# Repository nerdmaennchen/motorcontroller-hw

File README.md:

A somewhat easy to build two-layer PCB to controll BLDC-motors with.

The board is designed to have:
	- USB connection (every computer has a USB port but there are virtually no boards out there that offer a USB connection (without an FTDI in between))
	- up to 200W (tested) output power (theoretical -- when ignoring trace resistances -- maximum 900W)
	- digital Hall-Encoder interface
	- analog/absolute hall-encoder interface
	- BEMF measurement for hall-less operation
	- serial interface to cascade multiple BLDC-drivers over one USB interface
	- two PWM outputs for RC-servo motors
	- one connector to attach WS2812b LEDs
	- a layout that allows somewhat easy manufacturing by placing most parts on one layer (I've once built 15 pieces in 8h by hand soldering)
	
The board has four power domains:
	- internal 3.3V -- to power the microcontroller
	- USB-5V -- can power the internal 3.3V domain; protected from the external 5V domain with a diode thus protecting the USB-host from voltage spikes on the external 5V-domain
	- external 5V -- can power the internal 3.3V domain; powers the WS2812b LEDs and RC-servo motors

The board utilizes an STM32F401xx processor which is super nice to program, debug and due to its QFN48 footprint super easy to solder by hand -- as long as you have access to a rework station.
Software for the uC can be found here: https://github.com/nerdmaennchen/motorcontroller-uc-sw
Software for the USB-Host here: https://github.com/nerdmaennchen/motorcontroller-sw

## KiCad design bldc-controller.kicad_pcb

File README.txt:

Hey Lutz,

hier Adrian von FRT...wollte nochmal nachfragen wie's aussieht?
Wenn ich den vorletztten Commit richtig verstanden habe, gibt's ja
ne gut funktionierende Variante?

Sry, das ich da sonen bisschen Druck machen muss, aber uns läuft 
lamgsam die Zeit davon...

LG Adrian

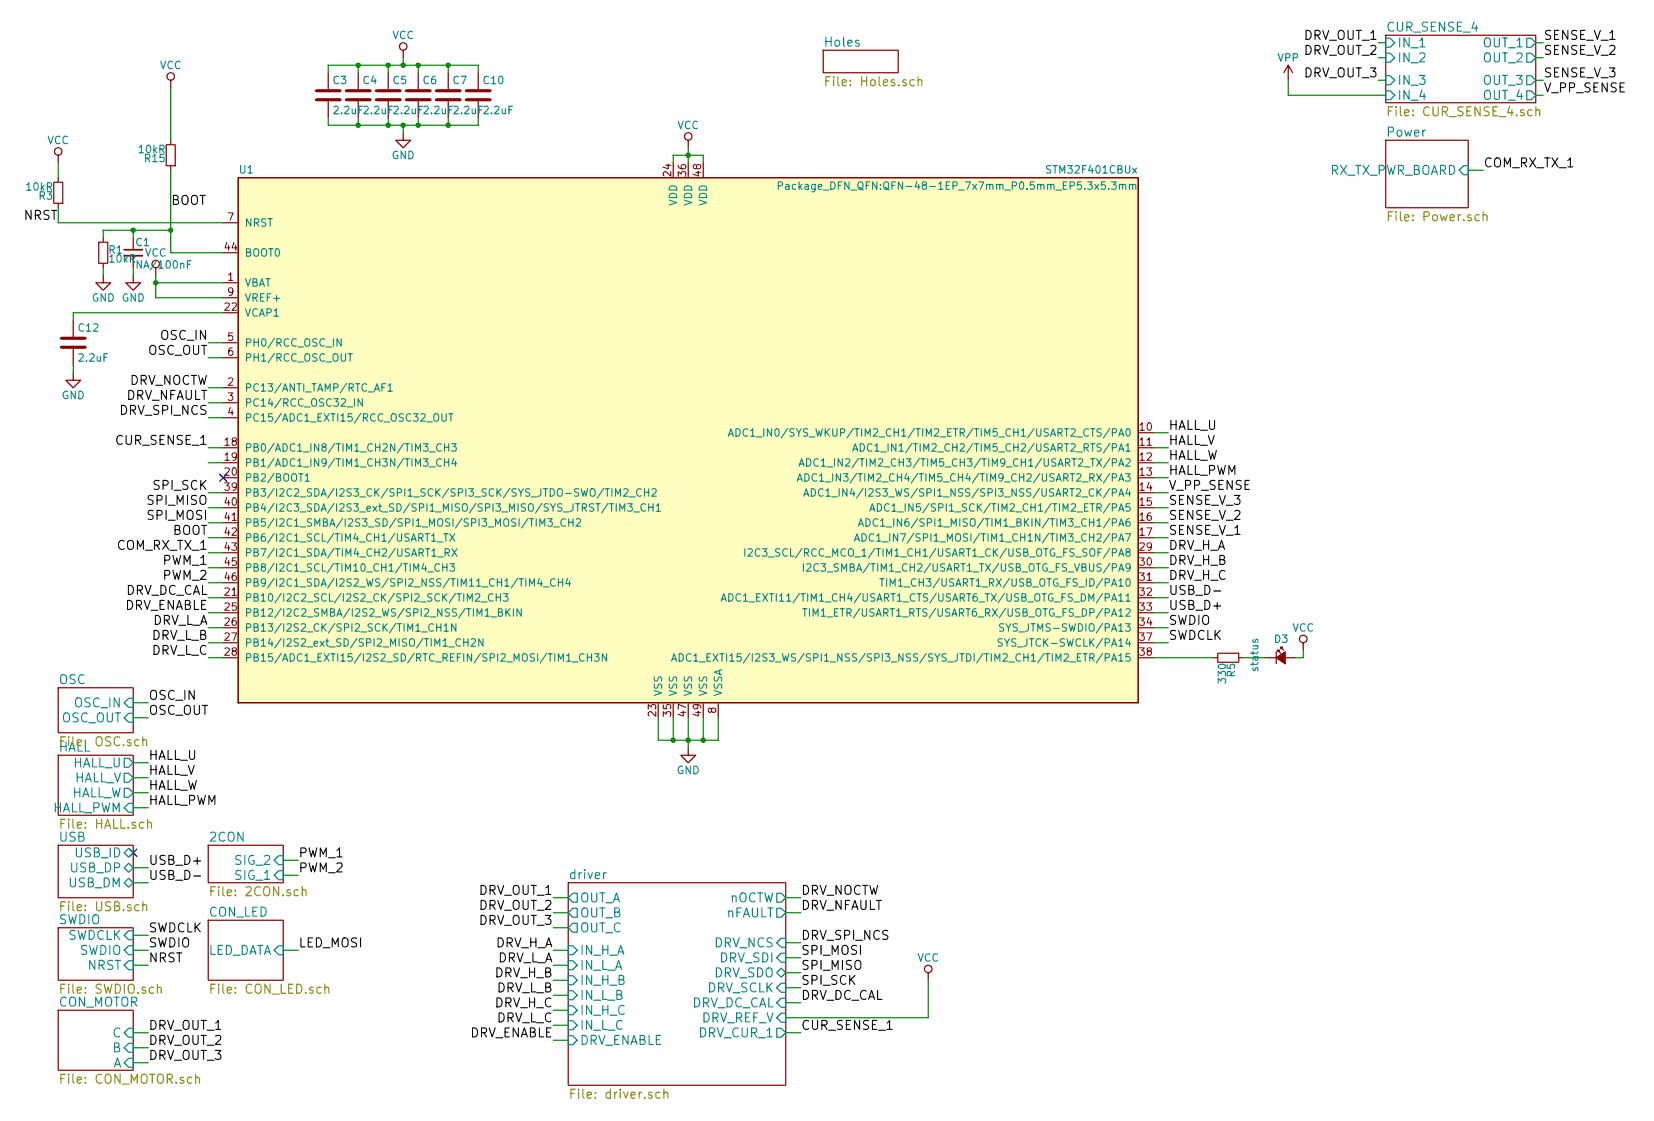
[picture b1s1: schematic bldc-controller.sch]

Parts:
C1: NA/100nF; C_0603_1608Metric
C3, C4, C5, C6, C7, C10, C12: 2.2uF; C_0603_1608Metric
D3: status; LED_0805_2012Metric
R1, R3, R15: 10kR; R_0603_1608Metric
R5: 330; R_0603_1608Metric
U1: STM32F401CBUx; QFN-48-1EP_7x7mm_P0.5mm_EP5.3x5.3mm

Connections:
/BOOT: C1.1, R1.1, R15.1, U1.42 (PB6/I2C1_SCL/TIM4_CH1/USART1_TX), U1.44 (BOOT0)
/COM_RX_TX_1: U1.43 (PB7/I2C1_SDA/TIM4_CH2/USART1_RX); also elsewhere on the board
/CUR_SENSE_1: U1.18 (PB0/ADC1_IN8/TIM1_CH2N/TIM3_CH3); also elsewhere on the board
/DRV_DC_CAL: U1.21 (PB10/I2C2_SCL/I2S2_CK/SPI2_SCK/TIM2_CH3); also elsewhere on the board
/DRV_ENABLE: U1.25 (PB12/I2C2_SMBA/I2S2_WS/SPI2_NSS/TIM1_BK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); also elsewhere on the board
/DRV_H_A: U1.29 (I2C3_SCL/RCC_MCO_1/TIM1_CH1/USART1_CK/U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); also elsewhere on the board
/DRV_H_B: U1.30 (I2C3_SMBA/TIM1_CH2/USART1_TX/USB_OTG_FS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); also elsewhere on the board
/DRV_H_C: U1.31 (TIM1_CH3/USART1_RX/USB_OTG_FS_ID/PA10); also elsewhere on the board
/DRV_L_A: U1.26 (PB13/I2S2_CK/SPI2_SCK/TIM1_CH1N); also elsewhere on the board
/DRV_L_B: U1.27 (PB14/I2S2_ext_SD/SPI2_MISO/TIM1_CH2N); also elsewhere on the board
/DRV_L_C: U1.28 (PB15/ADC1_EXTI15/I2S2_SD/RTC_REFIN/SPI2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); also elsewhere on the board
/DRV_NFAULT: U1.3 (PC14/RCC_OSC32_IN); also elsewhere on the board
/DRV_NOCTW: U1.2 (PC13/ANTI_TAMP/RTC_AF1); also elsewhere on the board
/DRV_SPI_NCS: U1.4 (PC15/ADC1_EXTI15/RCC_OSC32_OUT); also elsewhere on the board
/HALL_U: U1.10 (ADC1_IN0/SYS_WKUP/TIM2_CH1/TIM2_ETR/TIM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); also elsewhere on the board
/HALL_V: U1.11 (ADC1_IN1/TIM2_CH2/TIM5_CH2/USART2_RTS/P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); also elsewhere on the board
/HALL_W: U1.12 (ADC1_IN2/TIM2_CH3/TIM5_CH3/TIM9_CH1/USA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); also elsewhere on the board
/NRST: R3.1, U1.7 (NRST); also elsewhere on the board
/OSC_IN: U1.5 (PH0/RCC_OSC_IN); also elsewhere on the board
/OSC_OUT: U1.6 (PH1/RCC_OSC_OUT); also elsewhere on the board
/PWM_1: U1.45 (PB8/I2C1_SCL/TIM10_CH1/TIM4_CH3); also elsewhere on the board
/PWM_2: U1.46 (PB9/I2C1_SDA/I2S2_WS/SPI2_NSS/TIM11_CH1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); also elsewhere on the board
/SENSE_V_1: U1.17 (ADC1_IN7/SPI1_MOSI/TIM1_CH1N/TIM3_CH2/P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); also elsewhere on the board
/SENSE_V_2: U1.16 (ADC1_IN6/SPI1_MISO/TIM1_BKIN/TIM3_CH1/P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); also elsewhere on the board
/SENSE_V_3: U1.15 (ADC1_IN5/SPI1_SCK/TIM2_CH1/TIM2_ETR/PA5); also elsewhere on the board
/SPI_MISO: U1.40 (PB4/I2C3_SDA/I2S3_ext_SD/SPI1_MISO/SPI3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); also elsewhere on the board
/SPI_MOSI: U1.41 (PB5/I2C1_SMBA/I2S3_SD/SPI1_MOSI/SPI3_MO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); also elsewhere on the board
/SPI_SCK: U1.39 (PB3/I2C2_SDA/I2S3_CK/SPI1_SCK/SPI3_SCK/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); also elsewhere on the board
/SWDCLK: U1.37 (SYS_JTCK-SWCLK/PA14); also elsewhere on the board
/SWDIO: U1.34 (SYS_JTMS-SWDIO/PA13); also elsewhere on the board
/USB_D+: U1.33 (TIM1_ETR/USART1_RTS/USART6_RX/USB_OTG_F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); also elsewhere on the board
/USB_D-: U1.32 (ADC1_EXTI11/TIM1_CH4/USART1_CTS/USART6_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); also elsewhere on the board
/V_PP_SENSE: U1.14 (ADC1_IN4/I2S3_WS/SPI1_NSS/SPI3_NSS/USAR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); also elsewhere on the board
GND: C1.2, C3.2, C4.2, C5.2, C6.2, C7.2, C10.2, C12.2, R1.2, U1.8 (VSSA), U1.23 (VSS), U1.35 (VSS), U1.47 (VSS), U1.49 (VSS); also elsewhere on the board
unnamed: C12.1, U1.22 (VCAP1)
unnamed: D3.1 (K), R5.1
unnamed: R5.2, U1.38 (ADC1_EXTI15/I2S3_WS/SPI1_NSS/SPI3_NSS/S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)
VCC: C3.1, C4.1, C5.1, C6.1, C7.1, C10.1, D3.2 (A), R3.2, R15.2, U1.1 (VBAT), U1.9 (VREF+), U1.24 (VDD), U1.36 (VDD), U1.48 (VDD); also elsewhere on the board

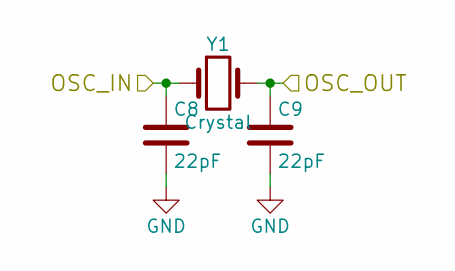
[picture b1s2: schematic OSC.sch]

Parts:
C8, C9: 22pF; C_0603_1608Metric
Y1: Crystal; Crystal_SMD_5032-2Pin_5.0x3.2mm

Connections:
/OSC_IN: C8.1, Y1.1; also elsewhere on the board
/OSC_OUT: C9.1, Y1.2; also elsewhere on the board
GND: C8.2, C9.2; also elsewhere on the board

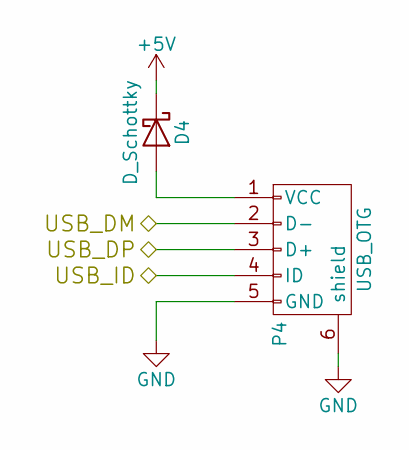
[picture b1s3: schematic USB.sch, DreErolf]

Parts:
D4: D_Schottky; D_SOD-323
P4: USB_OTG; USB_Micro-B_Molex_47346-0001

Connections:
+5V: D4.1 (K); also elsewhere on the board
/USB_D+: P4.3 (D+); also elsewhere on the board
/USB_D-: P4.2 (D-); also elsewhere on the board
GND: P4.5 (GND), P4.6 (shield); also elsewhere on the board
unnamed: D4.2 (A), P4.1 (VCC)

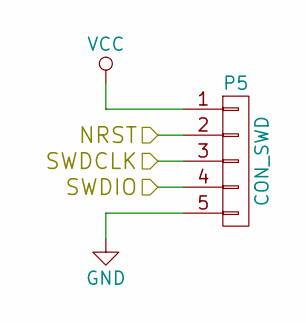
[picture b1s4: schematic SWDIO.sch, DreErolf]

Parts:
P5: CON_SWD; PinHeader_1x05_P2.54mm_Vertical

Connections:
/NRST: P5.2; also elsewhere on the board
/SWDCLK: P5.3; also elsewhere on the board
/SWDIO: P5.4; also elsewhere on the board
GND: P5.5; also elsewhere on the board
VCC: P5.1; also elsewhere on the board

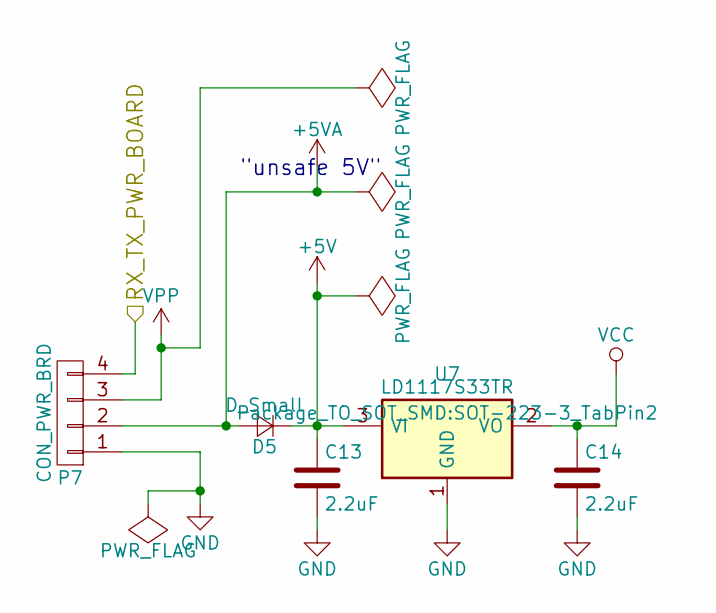
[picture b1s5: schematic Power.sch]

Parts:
C13, C14: 2.2uF; C_0603_1608Metric
D5: D_Small; D_SOD-323
P7: CON_PWR_BRD; PinHeader_1x04_P2.54mm_Vertical
U7: LD1117S33TR; SOT-223-3_TabPin2

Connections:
+5V: C13.1, D5.1 (K), U7.3 (VI); also elsewhere on the board
+5VA: D5.2 (A), P7.2; also elsewhere on the board
/COM_RX_TX_1: P7.4; also elsewhere on the board
GND: C13.2, C14.2, P7.1, U7.1 (GND); also elsewhere on the board
VCC: C14.1, U7.2 (VO); also elsewhere on the board
VPP: P7.3; also elsewhere on the board

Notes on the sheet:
"unsafe 5V"

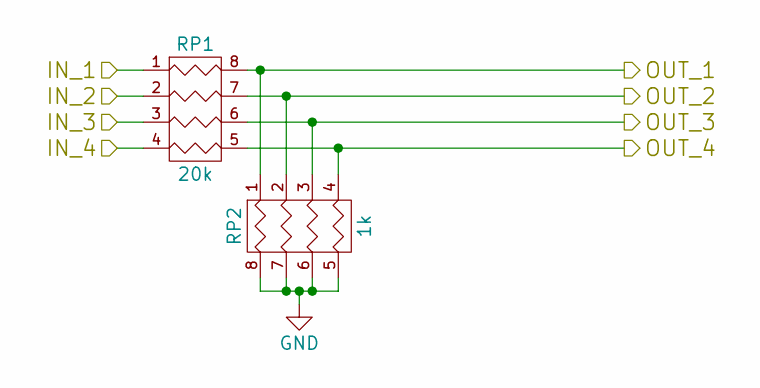
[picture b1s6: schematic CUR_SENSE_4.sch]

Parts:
RP1: 20k; R_Array_Concave_4x0603
RP2: 1k; R_Array_Concave_4x0603

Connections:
/DRV_OUT_1: RP1.1; also elsewhere on the board
/DRV_OUT_2: RP1.2; also elsewhere on the board
/DRV_OUT_3: RP1.3; also elsewhere on the board
/SENSE_V_1: RP1.8 (R1), RP2.1; also elsewhere on the board
/SENSE_V_2: RP1.7 (R2), RP2.2; also elsewhere on the board
/SENSE_V_3: RP1.6 (R3), RP2.3; also elsewhere on the board
/V_PP_SENSE: RP1.5 (R4), RP2.4; also elsewhere on the board
GND: RP2.5 (R4), RP2.6 (R3), RP2.7 (R2), RP2.8 (R1); also elsewhere on the board
VPP: RP1.4; also elsewhere on the board

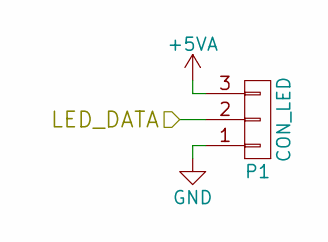
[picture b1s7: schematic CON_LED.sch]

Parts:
P1: CON_LED; PinHeader_1x03_P2.54mm_Vertical

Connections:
+5VA: P1.3; also elsewhere on the board
GND: P1.1; also elsewhere on the board

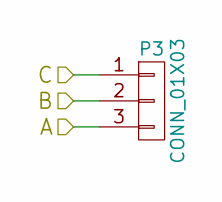
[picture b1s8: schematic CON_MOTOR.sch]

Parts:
P3: CONN_01X03; PinHeader_1x03_P2.54mm_Horizontal

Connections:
/DRV_OUT_1: P3.1; also elsewhere on the board
/DRV_OUT_2: P3.2; also elsewhere on the board
/DRV_OUT_3: P3.3; also elsewhere on the board

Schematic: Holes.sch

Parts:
P2, P8, P9, P10: MOUNTING; 1pin

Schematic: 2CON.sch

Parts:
J1: Conn_02x03_Odd_Even; PinHeader_2x03_P2.00mm_Horizontal

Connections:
+5VA: J1.3, J1.4; also elsewhere on the board
/PWM_1: J1.2; also elsewhere on the board
/PWM_2: J1.1; also elsewhere on the board
GND: J1.5, J1.6; also elsewhere on the board

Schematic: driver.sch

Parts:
C2: 22nF; C_0603_1608Metric
C11, C15, C16: 2.2uF; C_0603_1608Metric
C17, C18, C19, C21, C22, C23: 100nF; C_0603_1608Metric
C20: 10uF; CP_Elec_5x3
Q1, Q2, Q3, Q4, Q5, Q6: Q_NMOS_DGS; SOT1210
R2, R4: 10kR; R_0603_1608Metric
R6: 1R; R_0603_1608Metric
R7, R9, R10, R11, R13, R14: 10R; R_0603_1608Metric
R8, R12: .01; R_1206_3216Metric
U2: DRV8313; SOIC-48

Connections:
/CUR_SENSE_1: U2.21 (SO1); also elsewhere on the board
/DRV_DC_CAL: U2.8 (DC_CAL); also elsewhere on the board
/DRV_ENABLE: U2.12 (EN_GATE); also elsewhere on the board
/DRV_H_A: U2.13 (INH_A); also elsewhere on the board
/DRV_H_B: U2.15 (INH_B); also elsewhere on the board
/DRV_H_C: U2.17 (INH_C); also elsewhere on the board
/DRV_L_A: U2.14 (INL_A); also elsewhere on the board
/DRV_L_B: U2.16 (INL_B); also elsewhere on the board
/DRV_L_C: U2.18 (INL_C); also elsewhere on the board
/DRV_NFAULT: R4.2, U2.2 (nFAULT); also elsewhere on the board
/DRV_NOCTW: R2.2, U2.1 (nOCTW); also elsewhere on the board
/DRV_OUT_1: C17.1, Q1.3 (S), Q2.1 (D), U2.42 (SH_A); also elsewhere on the board
/DRV_OUT_2: C18.1, Q3.3 (S), Q4.1 (D), U2.37 (SH_B); also elsewhere on the board
/DRV_OUT_3: C19.1, Q5.3 (S), Q6.1 (D), U2.32 (SH_C); also elsewhere on the board
/DRV_SPI_NCS: U2.4 (nSCS); also elsewhere on the board
/SPI_MISO: U2.6 (SDO); also elsewhere on the board
/SPI_MOSI: U2.5 (SDI); also elsewhere on the board
/SPI_SCK: U2.7 (SCKL); also elsewhere on the board
GND: C11.2, C15.2, C16.2, C20.2, C21.2, C22.1, C23.1, R6.2, R8.2, R12.2, U2.24 (AGND), U2.26 (SP2), U2.27 (SN2), U2.28 (SP1), U2.46 (GND), U2.47 (GND), U2.48 (GND), U2.49 (PPAD); also elsewhere on the board
unnamed: C2.1, U2.10 (CP1)
unnamed: C2.2, U2.11 (CP2)
unnamed: C11.1, U2.9 (GVDD)
unnamed: C15.1, U2.19 (DVDD)
unnamed: C16.1, U2.23 (AVDD)
unnamed: C17.2, U2.44 (BST_A)
unnamed: C18.2, U2.39 (BST_B)
unnamed: C19.2, U2.34 (BST_C)
unnamed: C22.2, C23.2, Q2.3 (S), Q4.3 (S), Q6.3 (S), R8.1, R12.1, U2.29 (SN1), U2.30 (SL_C), U2.35 (SL_B), U2.40 (SL_A)
unnamed: Q1.2 (G), R7.1
unnamed: Q2.2 (G), R9.1
unnamed: Q3.2 (G), R10.1
unnamed: Q4.2 (G), R11.1
unnamed: Q5.2 (G), R13.1
unnamed: Q6.2 (G), R14.1
unnamed: R6.1, U2.3 (DTC)
unnamed: R7.2, U2.43 (GH_A)
unnamed: R9.2, U2.41 (GL_A)
unnamed: R10.2, U2.38 (GH_B)
unnamed: R11.2, U2.36 (GL_B)
unnamed: R13.2, U2.33 (GH_C)
unnamed: R14.2, U2.31 (GL_C)
VCC: R2.1, R4.1, U2.20 (REF), U2.45 (VDD_SPI); also elsewhere on the board
VPP: C20.1, C21.1, Q1.1 (D), Q3.1 (D), Q5.1 (D), U2.25 (PVDD); also elsewhere on the board

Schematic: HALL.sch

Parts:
P6: CON_HALL; PinHeader_1x05_P2.54mm_Horizontal
R16, R17, R18: 47kR; R_0603_1608Metric

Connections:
+5V: P6.1, R16.2, R17.2, R18.2; also elsewhere on the board
/HALL_U: P6.2, R16.1; also elsewhere on the board
/HALL_V: P6.3, R17.1; also elsewhere on the board
/HALL_W: P6.4, R18.1; also elsewhere on the board

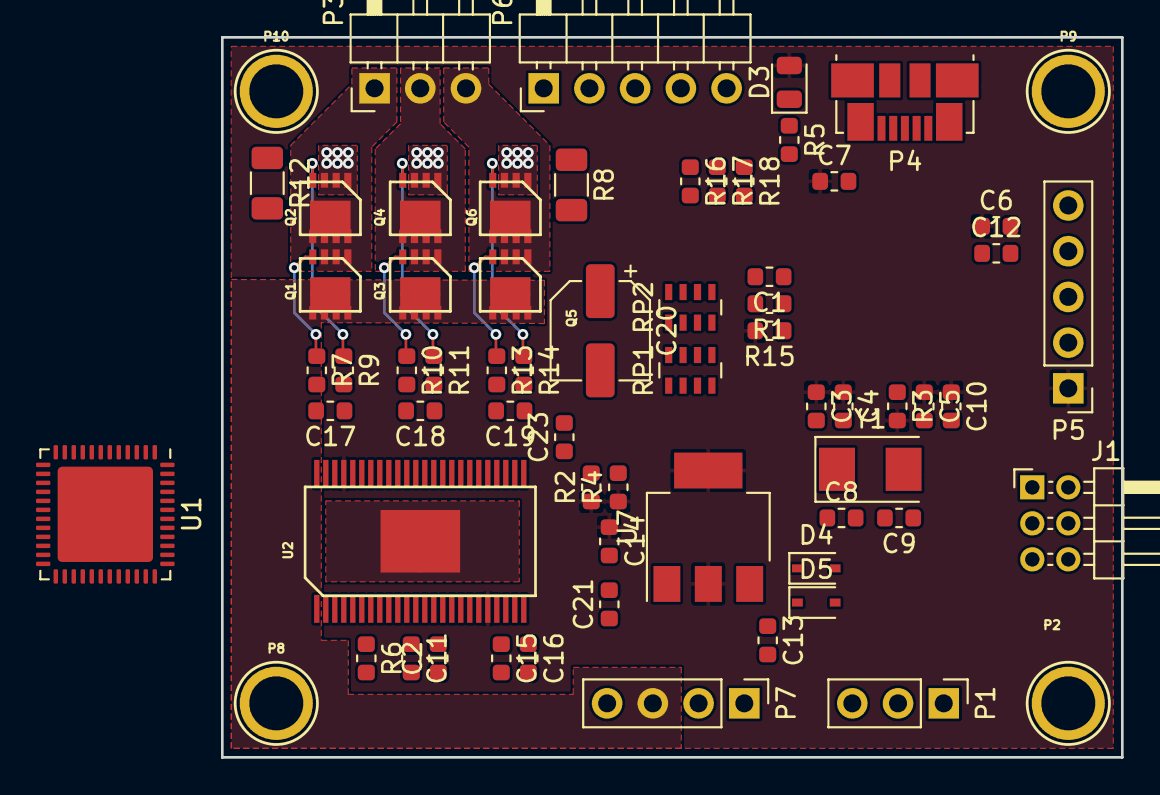
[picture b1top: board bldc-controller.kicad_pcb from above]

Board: 2 copper layers, 50.0 x 40.0 mm, 67 parts (1 on the bottom side), 67 nets.

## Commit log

2016-07-25 blubb
2016-08-17 routed
2016-08-19 fertig?
2016-08-19 bestellversion
2016-09-08 updated some stuff and added some more docu
2016-10-20 updated stuff
2016-10-24 i think im good with the schematics
2016-10-25 changed the maximum outpul voltage of the RC-Filter to VPP
2016-10-31 routed... at least for now
2016-10-31 some sugar
2016-11-01 well... actually we dont need those thwo parts since the bootloader can be entered from flash software
2016-11-01 even though Im pretty sure that resistor is actually not needed Id like to play safe and have it anyway
2016-11-07 corrected order version
2016-11-11 changed that capacitor to a more reasonable value
2016-11-11 small update
2016-12-15 updated gitignore
2016-12-22 Create README.txt
    Bitte lesen und antworten!
2017-01-11 some sugar coating and updated gerbers
2017-01-30 updated the readme -- this is _not_ a substitute to email me haha --
2017-03-23 we dont need those files
2017-05-07 droped those obsolete files
2017-05-07 updated the part here
2017-05-07 updated project timestamp (kicad does that aparently)
2017-05-07 dropped those obsolete files
2017-05-07 some cleanup
2017-05-07 the readme had to be renamed to make github realize this is the readme...
2017-05-07 finally added a license file
2020-01-22 long forgotten commit of something I did half a year ago -.-
